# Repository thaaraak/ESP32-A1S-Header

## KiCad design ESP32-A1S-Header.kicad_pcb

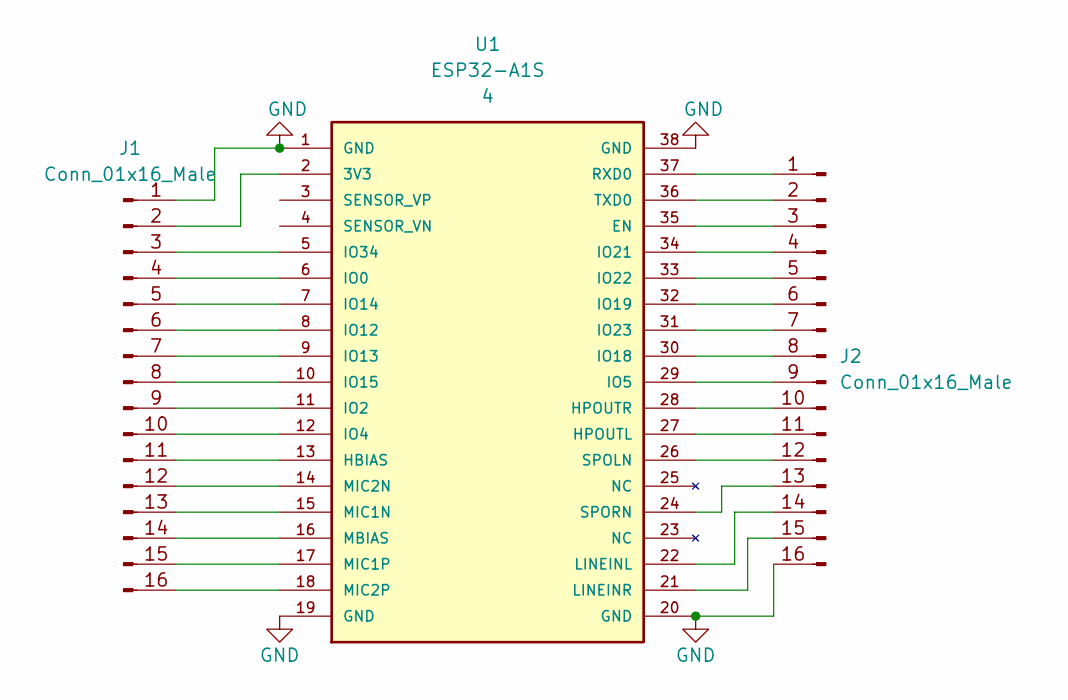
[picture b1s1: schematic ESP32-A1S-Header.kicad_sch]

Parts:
J1, J2: Conn_01x16_Male; PinHeader_1x16_P2.54mm_Vertical
U1: ESP32-A1S; ESP32-A1S-GND; PARTREV 4

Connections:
GND: J1.1, J2.16, U1.1 (GND), U1.19 (GND), U1.20 (GND), U1.38 (GND)
unnamed: J1.2, U1.2 (3V3)
unnamed: J1.3, U1.5 (IO34)
unnamed: J1.4, U1.6 (IO0)
unnamed: J1.5, U1.7 (IO14)
unnamed: J1.6, U1.8 (IO12)
unnamed: J1.7, U1.9 (IO13)
unnamed: J1.8, U1.10 (IO15)
unnamed: J1.9, U1.11 (IO2)
unnamed: J1.10, U1.12 (IO4)
unnamed: J1.11, U1.13 (HBIAS)
unnamed: J1.12, U1.14 (MIC2N)
unnamed: J1.13, U1.15 (MIC1N)
unnamed: J1.14, U1.16 (MBIAS)
unnamed: J1.15, U1.17 (MIC1P)
unnamed: J1.16, U1.18 (MIC2P)
unnamed: J2.15, U1.21 (LINEINR)
unnamed: J2.14, U1.22 (LINEINL)
unnamed: J2.13, U1.24 (SPORN)
unnamed: J2.12, U1.26 (SPOLN)
unnamed: J2.11, U1.27 (HPOUTL)
unnamed: J2.10, U1.28 (HPOUTR)
unnamed: J2.9, U1.29 (IO5)
unnamed: J2.8, U1.30 (IO18)
unnamed: J2.7, U1.31 (IO23)
unnamed: J2.6, U1.32 (IO19)
unnamed: J2.5, U1.33 (IO22)
unnamed: J2.4, U1.34 (IO21)
unnamed: J2.3, U1.35 (EN)
unnamed: J2.2, U1.36 (TXD0)
unnamed: J2.1, U1.37 (RXD0)

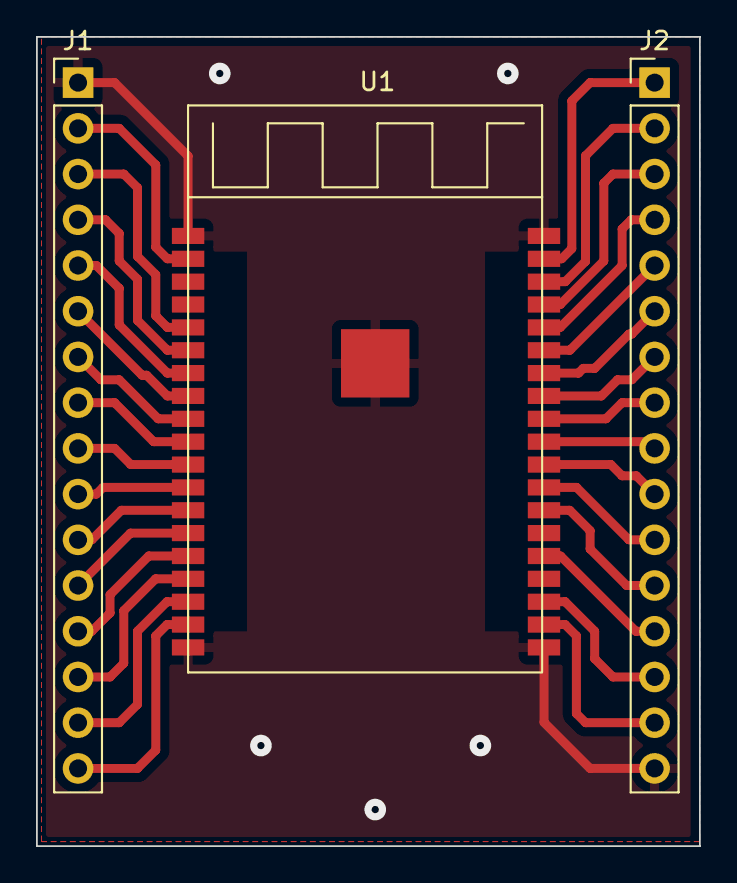
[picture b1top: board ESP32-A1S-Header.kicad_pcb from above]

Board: 2 copper layers, 36.8 x 45.0 mm, 3 parts (0 on the bottom side), 31 nets.
